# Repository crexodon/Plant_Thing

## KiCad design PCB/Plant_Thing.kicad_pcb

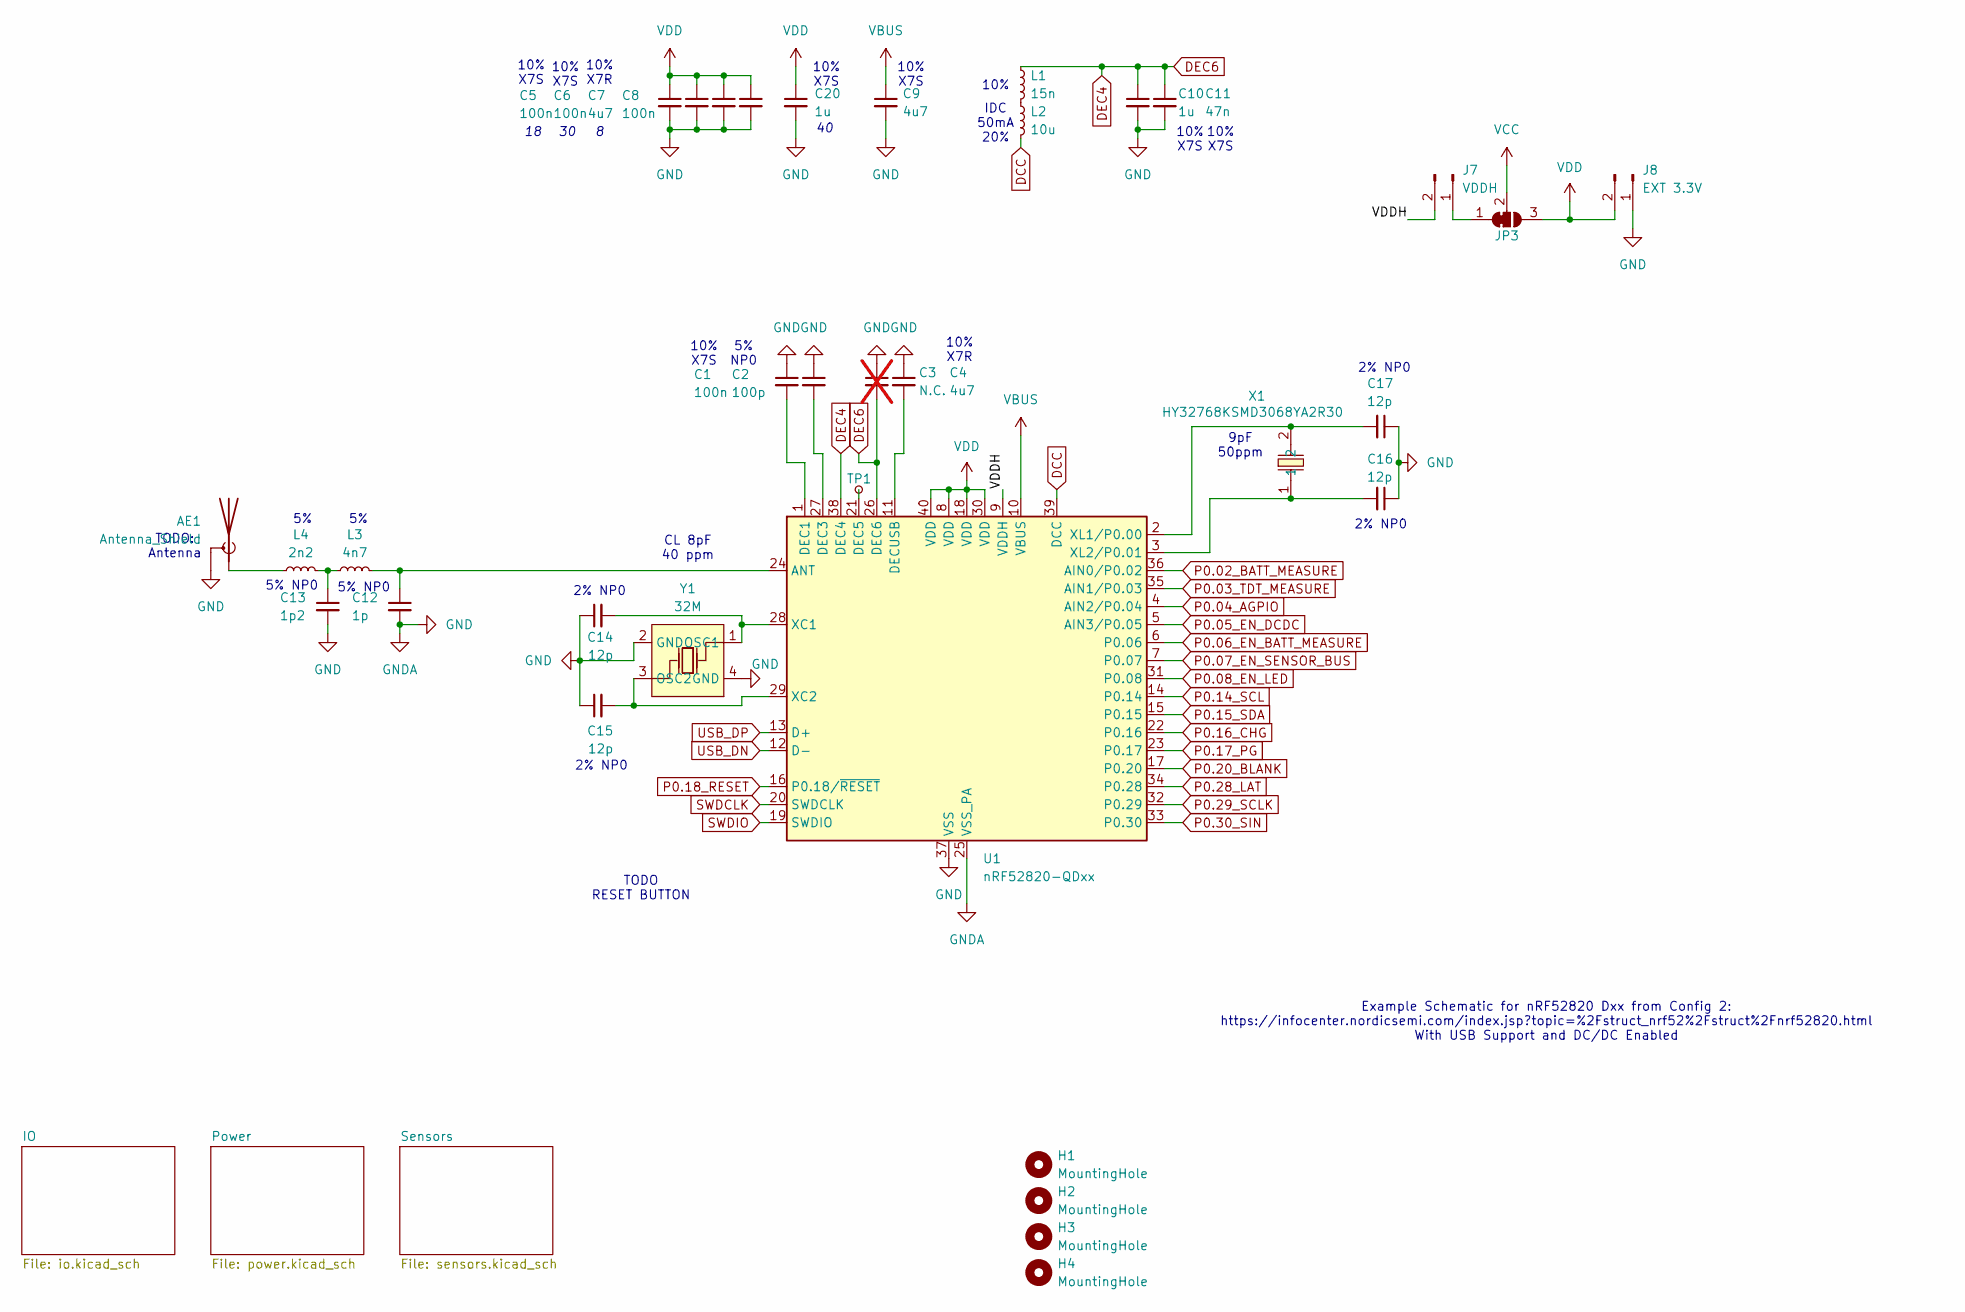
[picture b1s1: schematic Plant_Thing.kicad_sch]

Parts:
AE1: Antenna_Shield; Texas_SWRA117D_2.4GHz_Left
C1, C5, C6, C8: 100n; C_0402_1005Metric
C2: 100p; C_0402_1005Metric
C3: N.C.; not fitted
C4, C7, C9: 4u7; C_0603_1608Metric
C10, C20: 1u; C_0603_1608Metric
C11: 47n; C_0402_1005Metric
C12: 1p; C_0201_0603Metric
C13: 1p2; C_0201_0603Metric
C14, C15, C16, C17: 12p; C_0402_1005Metric
H1, H2, H3, H4: MountingHole; MountingHole_2.7mm_M2.5_DIN965
J7: VDDH; PinHeader_1x02_P2.54mm_Vertical
J8: EXT 3.3V; PinHeader_1x02_P2.54mm_Vertical
JP3: SolderJumper_3_Bridged12; SolderJumper-3_P1.3mm_Bridged12_RoundedPad1.0x1.5mm
L1: 15n; L_0603_1608Metric
L2: 10u; L_0603_1608Metric
L3: 4n7; L_0201_0603Metric
L4: 2n2; L_0201_0603Metric
TP1: TestPoint_Small; TestPoint_Pad_D1.0mm
U1: nRF52820-QDxx; QFN-40-1EP_5x5mm_P0.4mm_EP3.6x3.6mm
X1: HY32768KSMD3068YA2R30; CRYSTAL-SMD_L7.0-W3.2-LS7.5; LCSC Part C5265854
Y1: 32M; CRYSTAL-SMD_4P-L3.2-W2.5-BL; LCSC Part C9009

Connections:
/VDDH: J7.2, U1.9 (VDDH)
DCC: L2.2, U1.39 (DCC)
DEC4: C3.2, C10.1, C11.1, L1.1, U1.26 (DEC6), U1.38 (DEC4)
GND: AE1.2 (Shield), C1.1, C2.1, C3.1, C4.1, C5.2, C6.2, C7.2, C8.2, C9.2, C10.2, C11.2, C12.2, C13.2, C14.1, C15.1, C16.1, C17.1, C20.2, J8.1, U1.25 (VSS_PA), U1.37 (VSS), U1.41 (VSS), Y1.2 (GND), Y1.4 (GND); also elsewhere on the board
unnamed: AE1.1 (A), L4.1
unnamed: C13.1, L3.1, L4.2
unnamed: J7.1, JP3.1 (A)
unnamed: L1.2, L2.1
unnamed: C12.1, L3.2, U1.24 (ANT)
unnamed: C1.2, U1.1 (DEC1)
unnamed: C2.2, U1.27 (DEC3)
unnamed: TP1.1, U1.21 (DEC5)
unnamed: C4.2, U1.11 (DECUSB)
unnamed: C14.2, U1.28 (XC1), Y1.1 (OSC1)
unnamed: C15.2, U1.29 (XC2), Y1.3 (OSC2)
unnamed: C17.2, U1.2 (XL1/P0.00), X1.2
unnamed: C16.2, U1.3 (XL2/P0.01), X1.1
P0.02_BATT_MEASURE: U1.36 (AIN0/P0.02); also elsewhere on the board
P0.03_TDT_MEASURE: U1.35 (AIN1/P0.03); also elsewhere on the board
P0.04_AGPIO: U1.4 (AIN2/P0.04); also elsewhere on the board
P0.05_EN_DCDC: U1.5 (AIN3/P0.05); also elsewhere on the board
P0.06_EN_BATT_MEASURE: U1.6 (P0.06); also elsewhere on the board
P0.07_EN_SENSOR_BUS: U1.7 (P0.07); also elsewhere on the board
P0.08_EN_LED: U1.31 (P0.08); also elsewhere on the board
P0.14_SCL: U1.14 (P0.14); also elsewhere on the board
P0.15_SDA: U1.15 (P0.15); also elsewhere on the board
P0.16_CHG: U1.22 (P0.16); also elsewhere on the board
P0.17_PG: U1.23 (P0.17); also elsewhere on the board
P0.18_RESET: U1.16 (P0.18/~RESET); also elsewhere on the board
P0.20_BLANK: U1.17 (P0.20); also elsewhere on the board
P0.28_LAT: U1.34 (P0.28); also elsewhere on the board
P0.29_SCLK: U1.32 (P0.29); also elsewhere on the board
P0.30_SIN: U1.33 (P0.30); also elsewhere on the board
SWDCLK: U1.20 (SWDCLK); also elsewhere on the board
SWDIO: U1.19 (SWDIO); also elsewhere on the board
USB_DN: U1.12 (D-); also elsewhere on the board
USB_DP: U1.13 (D+); also elsewhere on the board
VBUS: C9.1, U1.10 (VBUS); also elsewhere on the board
VCC: JP3.2 (C); also elsewhere on the board
VDD: C5.1, C6.1, C7.1, C8.1, C20.1, J8.2, JP3.3 (B), U1.8 (VDD), U1.18 (VDD), U1.30 (VDD), U1.40 (VDD); also elsewhere on the board

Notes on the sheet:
10% X7S
TODO: Antenna
10% X7R
2% NP0
10%
IDC 50mA 20%
5% NP0
5% NP0
9pF 50ppm
CL 8pF 40 ppm
Example Schematic for nRF52820 Dxx from Config 2: https://infocenter.nordicsemi.com/index.jsp?topic=%2Fstruct_nrf52%2Fstruct%2Fnrf52820.html With USB Support and DC/DC Enabled
TODO RESET BUTTON

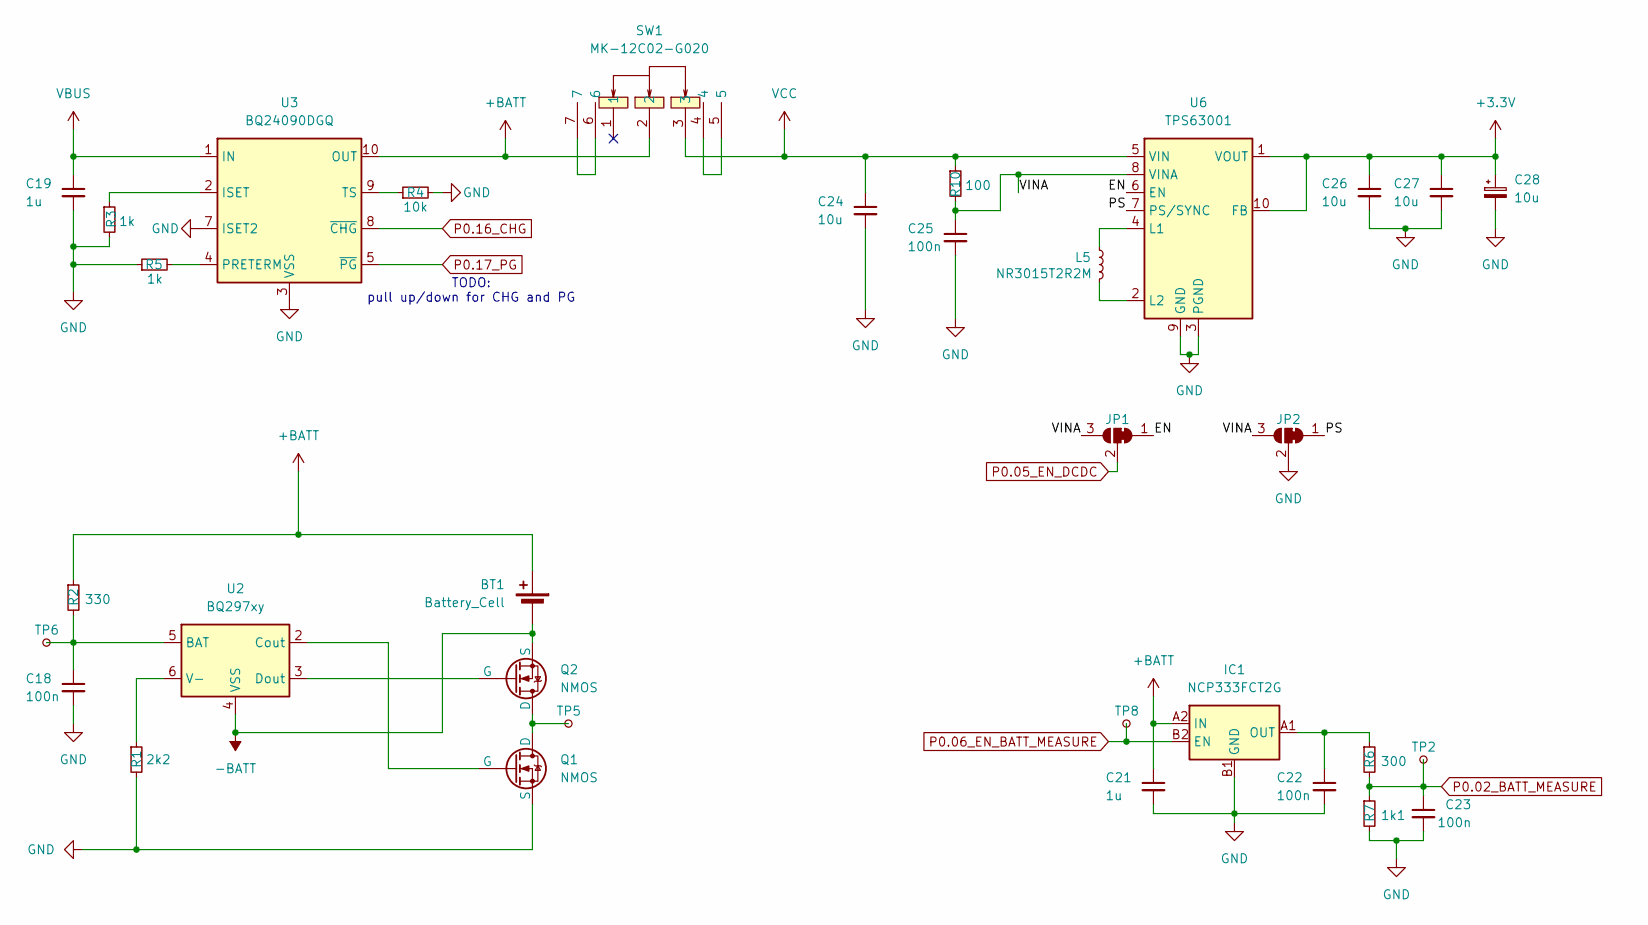
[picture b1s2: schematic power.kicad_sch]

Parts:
BT1: Battery_Cell; JST_PH_S2B-PH-K_1x02_P2.00mm_Horizontal
C18, C22, C23: 100n; C_0402_1005Metric
C19: 1u; C_0603_1608Metric
C21: 1u; C_0402_1005Metric
C24, C26, C27: 10u; C_0603_1608Metric
C25: 100n; C_0603_1608Metric
C28: 10u; CP_Elec_5x4.4
IC1: NCP333FCT2G; BGA4C40P2X2_76X76X63; Manufacturer_Part_Number NCP333FCT2G; Mouser Part Number 863-NCP333FCT2G
JP1, JP2: SolderJumper_3_Bridged12; SolderJumper-3_P1.3mm_Bridged12_RoundedPad1.0x1.5mm
L5: NR3015T2R2M; L_Taiyo-Yuden_NR-30xx
Q1, Q2: NMOS; SOT-23
R1: 2k2; R_0402_1005Metric
R2: 330; R_0402_1005Metric
R3, R5: 1k; R_0402_1005Metric
R4: 10k; R_0402_1005Metric
R6: 300; R_0402_1005Metric
R7: 1k1; R_0402_1005Metric
R10: 100; R_0402_1005Metric
SW1: MK-12C02-G020; SW-SMD_MK-12C02-G020; LCSC Part C963206
TP2, TP5, TP6, TP8: TestPoint_Small; TestPoint_Pad_D1.0mm
U2: BQ297xy; WSON-6_1.5x1.5mm_P0.5mm
U3: BQ24090DGQ; HVSSOP-10-1EP_3x3mm_P0.5mm_EP1.57x1.88mm_ThermalVias
U6: TPS63001; Texas_DRC0010J_ThermalVias

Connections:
+3.3V: C26.1, C27.1, C28.1, U6.1 (VOUT), U6.10 (FB); also elsewhere on the board
+BATT: BT1.1 (+), C21.1, IC1.A2 (IN), R2.1, SW1.2, U3.10 (OUT)
-BATT: BT1.2 (-), Q2.3 (S), U2.4 (VSS)
/Power/EN: JP1.1 (A), U6.6 (EN)
/Power/PS: JP2.1 (A), U6.7 (PS/SYNC)
/Power/VINA: C25.1, JP1.3 (B), JP2.3 (B), R10.2, U6.8 (VINA)
GND: C18.2, C19.2, C21.2, C22.2, C23.2, C24.2, C25.2, C26.2, C27.2, C28.2, IC1.B1 (GND), JP2.2 (C), Q1.3 (S), R1.2, R3.2, R4.2, R5.1, R7.2, U3.3 (VSS), U3.7 (ISET2), U3.11 (VSS), U6.3 (PGND), U6.9 (GND), U6.11 (PGND); also elsewhere on the board
unnamed: C22.1, IC1.A1 (OUT), R6.1
unnamed: Q1.1 (D), Q2.1 (D), TP5.1
unnamed: Q1.2 (G), U2.2 (Cout)
unnamed: Q2.2 (G), U2.3 (Dout)
unnamed: SW1.4, SW1.5
unnamed: SW1.6, SW1.7
unnamed: C18.1, R2.2, TP6.1, U2.5 (BAT)
unnamed: R1.1, U2.6 (V-)
unnamed: R3.1, U3.2 (ISET)
unnamed: R5.2, U3.4 (PRETERM)
unnamed: R4.1, U3.9 (TS)
unnamed: L5.1, U6.4 (L1)
unnamed: L5.2, U6.2 (L2)
P0.02_BATT_MEASURE: C23.1, R6.2, R7.1, TP2.1; also elsewhere on the board
P0.05_EN_DCDC: JP1.2 (C); also elsewhere on the board
P0.06_EN_BATT_MEASURE: IC1.B2 (EN), TP8.1; also elsewhere on the board
P0.16_CHG: U3.8 (~CHG); also elsewhere on the board
P0.17_PG: U3.5 (~PG); also elsewhere on the board
VBUS: C19.1, U3.1 (IN); also elsewhere on the board
VCC: C24.1, R10.1, SW1.3, U6.5 (VIN); also elsewhere on the board

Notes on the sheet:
TODO: pull up/down for CHG and PG

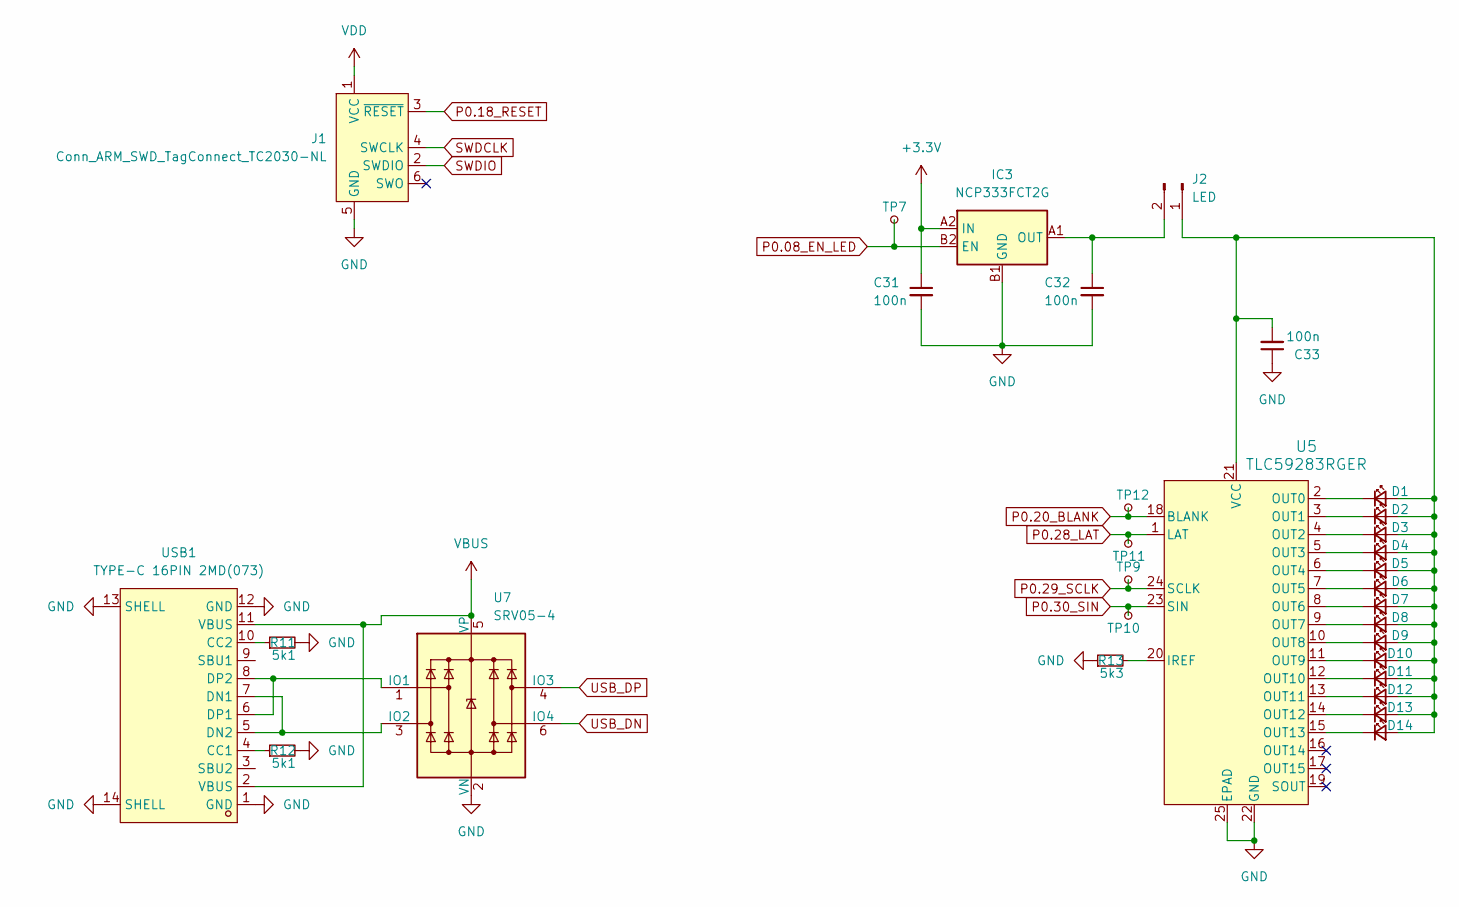
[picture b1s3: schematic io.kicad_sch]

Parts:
C31, C32, C33: 100n; C_0402_1005Metric
D1, D2, D3, D4, D5, D6, D7, D8, D9, D10, D11, D12, D13, D14: LED_Small; LED_0805_2012Metric
IC3: NCP333FCT2G; BGA4C40P2X2_76X76X63; Manufacturer_Part_Number NCP333FCT2G; Mouser Part Number 863-NCP333FCT2G
J1: Conn_ARM_SWD_TagConnect_TC2030-NL; Tag-Connect_TC2030-IDC-NL_2x03_P1.27mm_Vertical
J2: LED; PinHeader_1x02_P2.54mm_Vertical
R11, R12: 5k1; R_0402_1005Metric
R13: 5k3; R_0402_1005Metric
TP7, TP9, TP10, TP11, TP12: TestPoint_Small; TestPoint_Pad_D1.0mm
U5: TLC59283RGER; RGE24_2P1X2P1_TEX
U7: SRV05-4; SOT-23-6
USB1: TYPE-C 16PIN 2MD(073); USB-C-SMD_TYPE-C-6PIN-2MD-073; LCSC Part C2765186

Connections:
+3.3V: C31.1, IC3.A2 (IN); also elsewhere on the board
GND: C31.2, C32.2, C33.1, IC3.B1 (GND), J1.5 (GND), R11.2, R12.2, R13.1, U5.22 (GND), U5.25 (EPAD), U7.2 (VN), USB1.1 (GND), USB1.12 (GND), USB1.13 (SHELL), USB1.14 (SHELL); also elsewhere on the board
unnamed: C33.2, D1.2 (A), D2.2 (A), D3.2 (A), D4.2 (A), D5.2 (A), D6.2 (A), D7.2 (A), D8.2 (A), D9.2 (A), D10.2 (A), D11.2 (A), D12.2 (A), D13.2 (A), D14.2 (A), J2.1, U5.21 (VCC)
unnamed: D1.1 (K), U5.2 (OUT0)
unnamed: D2.1 (K), U5.3 (OUT1)
unnamed: D3.1 (K), U5.4 (OUT2)
unnamed: D4.1 (K), U5.5 (OUT3)
unnamed: D5.1 (K), U5.6 (OUT4)
unnamed: D6.1 (K), U5.7 (OUT5)
unnamed: D7.1 (K), U5.8 (OUT6)
unnamed: D8.1 (K), U5.9 (OUT7)
unnamed: D9.1 (K), U5.10 (OUT8)
unnamed: D10.1 (K), U5.11 (OUT9)
unnamed: D11.1 (K), U5.12 (OUT10)
unnamed: D12.1 (K), U5.13 (OUT11)
unnamed: D13.1 (K), U5.14 (OUT12)
unnamed: D14.1 (K), U5.15 (OUT13)
unnamed: C32.1, IC3.A1 (OUT), J2.2
unnamed: R13.2, U5.20 (IREF)
unnamed: U7.1 (IO1), USB1.6 (DP1), USB1.8 (DP2)
unnamed: U7.3 (IO2), USB1.5 (DN2), USB1.7 (DN1)
unnamed: R12.1, USB1.4 (CC1)
unnamed: R11.1, USB1.10 (CC2)
P0.08_EN_LED: IC3.B2 (EN), TP7.1; also elsewhere on the board
P0.18_RESET: J1.3 (~RESET); also elsewhere on the board
P0.20_BLANK: TP12.1, U5.18 (BLANK); also elsewhere on the board
P0.28_LAT: TP11.1, U5.1 (LAT); also elsewhere on the board
P0.29_SCLK: TP9.1, U5.24 (SCLK); also elsewhere on the board
P0.30_SIN: TP10.1, U5.23 (SIN); also elsewhere on the board
SWDCLK: J1.4 (SWCLK); also elsewhere on the board
SWDIO: J1.2 (SWDIO); also elsewhere on the board
USB_DN: U7.6 (IO4); also elsewhere on the board
USB_DP: U7.4 (IO3); also elsewhere on the board
VBUS: U7.5 (VP), USB1.2 (VBUS), USB1.11 (VBUS); also elsewhere on the board
VDD: J1.1 (VCC); also elsewhere on the board

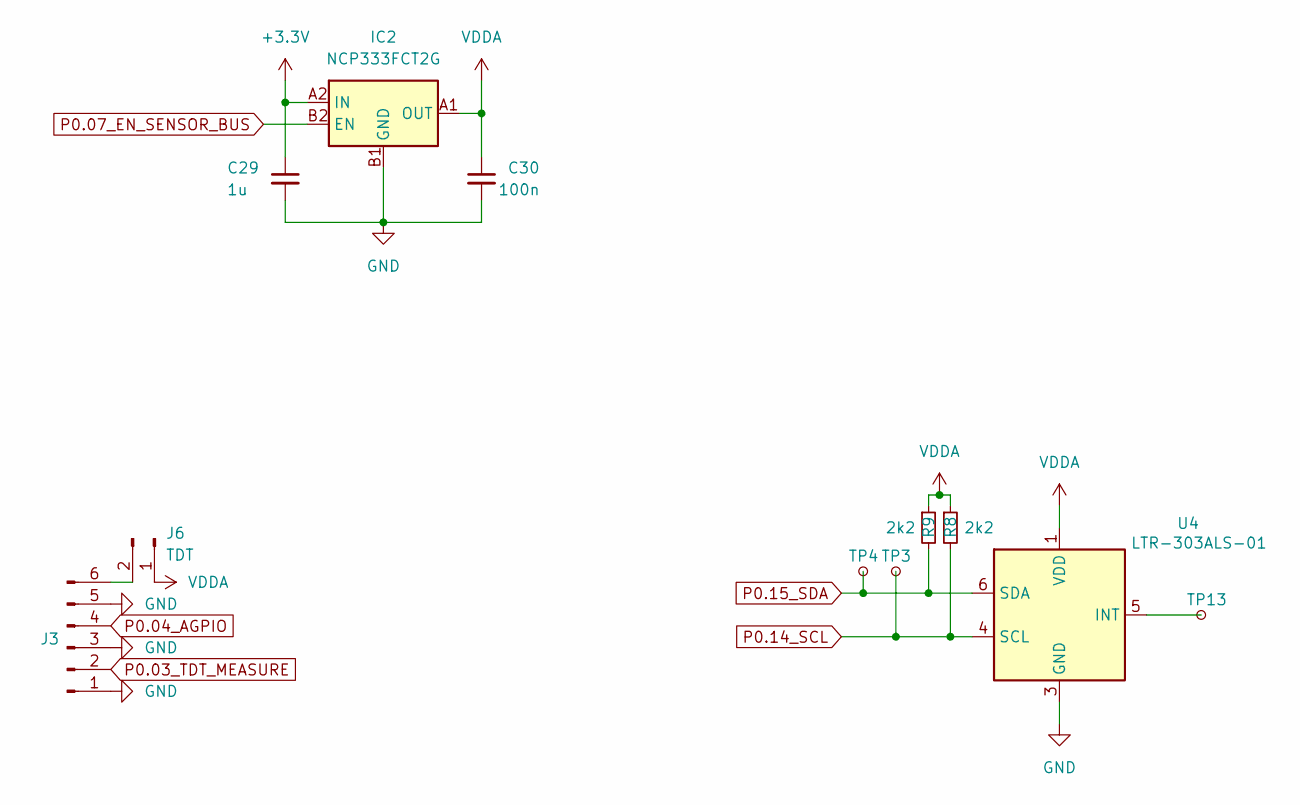
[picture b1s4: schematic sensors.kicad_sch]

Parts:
C29: 1u; C_0402_1005Metric
C30: 100n; C_0402_1005Metric
IC2: NCP333FCT2G; BGA4C40P2X2_76X76X63; Manufacturer_Part_Number NCP333FCT2G; Mouser Part Number 863-NCP333FCT2G
J3: Conn_01x06_Pin; PinHeader_1x06_P2.54mm_Vertical
J6: TDT; PinHeader_1x02_P2.54mm_Vertical
R8, R9: 2k2; R_0402_1005Metric
TP3, TP4, TP13: TestPoint_Small; TestPoint_Pad_D1.0mm
U4: LTR-303ALS-01; Lite-On_LTR-303ALS-01

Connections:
+3.3V: C29.1, IC2.A2 (IN); also elsewhere on the board
GND: C29.2, C30.2, IC2.B1 (GND), J3.1, J3.3, J3.5, U4.3 (GND); also elsewhere on the board
unnamed: J3.6, J6.2
unnamed: TP13.1, U4.5 (INT)
P0.03_TDT_MEASURE: J3.2; also elsewhere on the board
P0.04_AGPIO: J3.4; also elsewhere on the board
P0.07_EN_SENSOR_BUS: IC2.B2 (EN); also elsewhere on the board
P0.14_SCL: R8.2, TP3.1, U4.4 (SCL); also elsewhere on the board
P0.15_SDA: R9.2, TP4.1, U4.6 (SDA); also elsewhere on the board
VDDA: C30.1, IC2.A1 (OUT), J6.1, R8.1, R9.1, U4.1 (VDD)

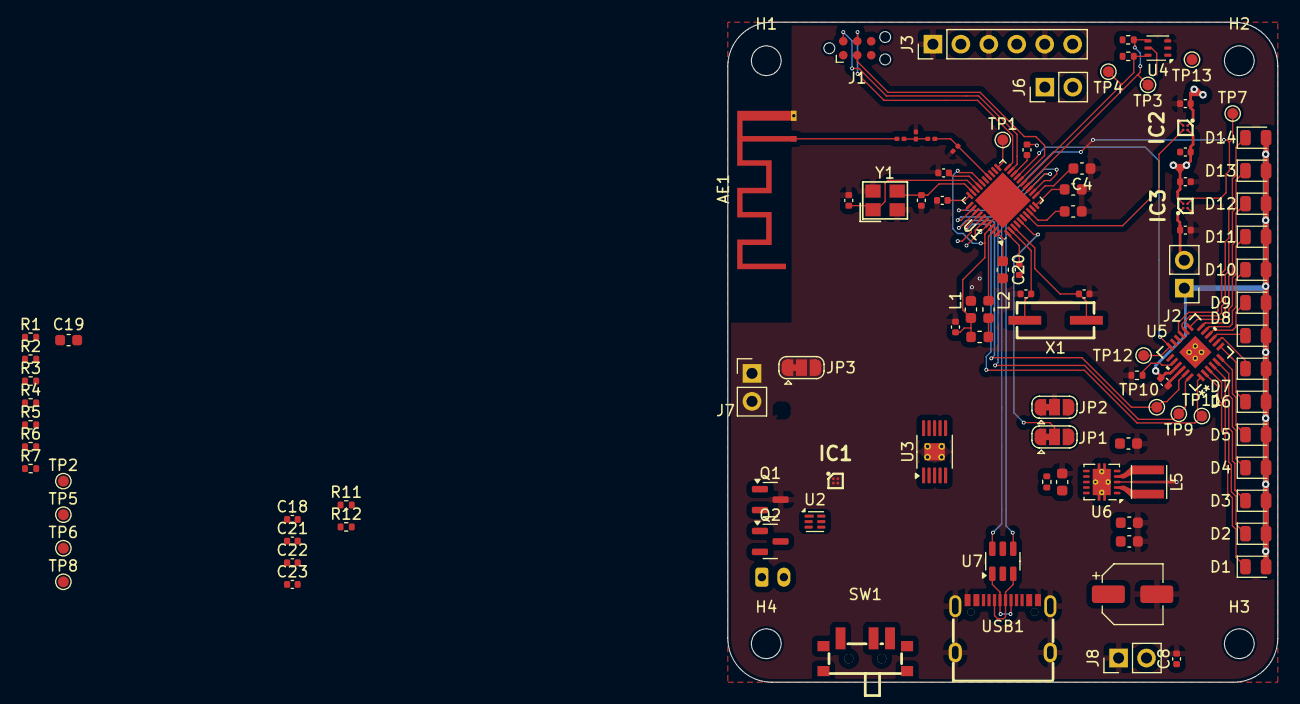
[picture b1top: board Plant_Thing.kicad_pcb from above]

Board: 4 copper layers, 50.0 x 60.0 mm, 108 parts (1 on the bottom side), 83 nets.

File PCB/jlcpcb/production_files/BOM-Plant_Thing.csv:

Comment,Designator,Footprint,LCSC
TYPE-C 16PIN 2MD(073),USB1,USB-C-SMD_TYPE-C-6PIN-2MD-073,C2765186
HY32768KSMD3068YA2R30,X1,CRYSTAL-SMD_L7.0-W3.2-LS7.5,C5265854
32M,Y1,CRYSTAL-SMD_4P-L3.2-W2.5-BL,C9009
MK-12C02-G020,SW1,SW-SMD_MK-12C02-G020,C963206
100n,C1,C_0402_1005Metric,
TestPoint_Small,TP1,TestPoint_Pad_D1.0mm,
100n,C8,C_0402_1005Metric,
1p2,C13,C_0201_0603Metric,
SRV05-4,U7,SOT-23-6,
12p,C16,C_0402_1005Metric,
10u,C27,C_0603_1608Metric,
TestPoint_Small,TP12,TestPoint_Pad_D1.0mm,
TestPoint_Small,TP9,TestPoint_Pad_D1.0mm,
12p,C14,C_0402_1005Metric,
TestPoint_Small,TP4,TestPoint_Pad_D1.0mm,
100n,C5,C_0402_1005Metric,
TestPoint_Small,TP2,TestPoint_Pad_D1.0mm,
BQ24090DGQ,U3,HVSSOP-10-1EP_3x3mm_P0.5mm_EP1.57x1.88mm_ThermalVias,
LED_Small,D4,LED_0805_2012Metric,
LED_Small,D1,LED_0805_2012Metric,
TestPoint_Small,TP6,TestPoint_Pad_D1.0mm,
TLC59283RGER,U5,RGE24_2P1X2P1_TEX,
12p,C15,C_0402_1005Metric,
30k,R6,R_0402_1005Metric,
LED_Small,D10,LED_0805_2012Metric,
10u,L2,L_0603_1608Metric,
2k2,R9,R_0402_1005Metric,
LED_Small,D6,LED_0805_2012Metric,
EXT 3.3V,J8,PinHeader_1x02_P2.54mm_Vertical,
1p,C12,C_0201_0603Metric,
10u,C26,C_0603_1608Metric,
5k1,R11,R_0402_1005Metric,
2k2,R1,R_0402_1005Metric,
330,R2,R_0402_1005Metric,
VDDH,J7,PinHeader_1x02_P2.54mm_Vertical,
NR3015T2R2M,L5,L_Taiyo-Yuden_NR-30xx,
1u,C29,C_0402_1005Metric,
TDT,J6,PinHeader_1x02_P2.54mm_Vertical,
Conn_01x06_Pin,J3,PinHeader_1x06_P2.54mm_Vertical,
LED_Small,D11,LED_0805_2012Metric,
TestPoint_Small,TP3,TestPoint_Pad_D1.0mm,
LED_Small,D15,LED_0805_2012Metric,
NMOS,Q2,SOT-23,
1u,C19,C_0603_1608Metric,
LED_Small,D2,LED_0805_2012Metric,
NCP333FCT2G,IC2,BGA4C40P2X2_76X76X63,
10u,C24,C_0603_1608Metric,
330u,C28,CP_Elec_10x10,
12p,C17,C_0402_1005Metric,
5k3,R13,R_0402_1005Metric,
nRF52820-QDxx,U1,QFN-40-1EP_5x5mm_P0.4mm_EP3.6x3.6mm,
LED_Small,D12,LED_0805_2012Metric,
LED,J2,PinHeader_1x02_P2.54mm_Vertical,
47n,C11,C_0402_1005Metric,
LED_Small,D7,LED_0805_2012Metric,
LED_Small,D14,LED_0805_2012Metric,
110k,R7,R_0402_1005Metric,
LTR-303ALS-01,U4,Lite-On_LTR-303ALS-01,
1k,R5,R_0402_1005Metric,
LED_Small,D9,LED_0805_2012Metric,
10k,R15,R_0402_1005Metric,
10k,R14,R_0402_1005Metric,
100n,C22,C_0402_1005Metric,
100n,C23,C_0402_1005Metric,
2n2,L4,L_0201_0603Metric,
LED_Small,D8,LED_0805_2012Metric,
Antenna_Shield,AE1,Texas_SWRA117D_2.4GHz_Left,
5k1,R12,R_0402_1005Metric,
BQ297xy,U2,WSON-6_1.5x1.5mm_P0.5mm,
1u,C20,C_0603_1608Metric,
TestPoint_Small,TP13,TestPoint_Pad_D1.0mm,
15n,L1,L_0603_1608Metric,
4u7,C7,C_0603_1608Metric,
10k,R4,R_0402_1005Metric,
TPS63001,U6,Texas_DRC0010J_ThermalVias,
TestPoint_Small,TP8,TestPoint_Pad_D1.0mm,
100p,C2,C_0402_1005Metric,
LED_Small,D5,LED_0805_2012Metric,
1u,C21,C_0402_1005Metric,
100n,C6,C_0402_1005Metric,
1k,R3,R_0402_1005Metric,
100n,C18,C_0402_1005Metric,
LED_Small,D13,LED_0805_2012Metric,
100n,C33,C_0402_1005Metric,
4u7,C9,C_0603_1608Metric,
NCP333FCT2G,IC1,BGA4C40P2X2_76X76X63,
100n,C30,C_0402_1005Metric,
100n,C25,C_0603_1608Metric,
4u7,C4,C_0603_1608Metric,
TestPoint_Small,TP11,TestPoint_Pad_D1.0mm,
LED_Small,D3,LED_0805_2012Metric,
2k2,R8,R_0402_1005Metric,
SW_Push_Dual,SW2,SW_Push_1P1T_XKB_TS-1187A,
100,R10,R_0402_1005Metric,
4n7,L3,L_0201_0603Metric,
TestPoint_Small,TP5,TestPoint_Pad_D1.0mm,
1u,C10,C_0603_1608Metric,
NMOS,Q1,SOT-23,
TestPoint_Small,TP10,TestPoint_Pad_D1.0mm,
Battery_Cell,BT1,JST_PH_S2B-PH-K_1x02_P2.00mm_Horizontal,

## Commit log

2024-04-13 Initial Commit and creation of pcb project with kicad
2024-04-13 added reference schematic for nrf52820 and placed components for power
2024-04-13 Added more power components
2024-04-15 Added more components and added most needed values for the nrf example schematic
2024-04-25 Added the Calathea Leaf as the outline and artwork for the project
2024-04-25 Added LED Driver IC for the led bar inside the calathea leaf
2024-04-27 added dcdc for external components. Changed board edge to a rect for easier dev board routuing.
2024-04-27 redid the pcb layout for a more bigger devboard approach. Added a few more components and the antenna.
2024-04-30 Added more Components
2024-05-02 Continued on Devboard
2024-05-27 Finished Devboard
2024-05-27 moved project to devboard folder, added README with schematic, images and description of devboard
